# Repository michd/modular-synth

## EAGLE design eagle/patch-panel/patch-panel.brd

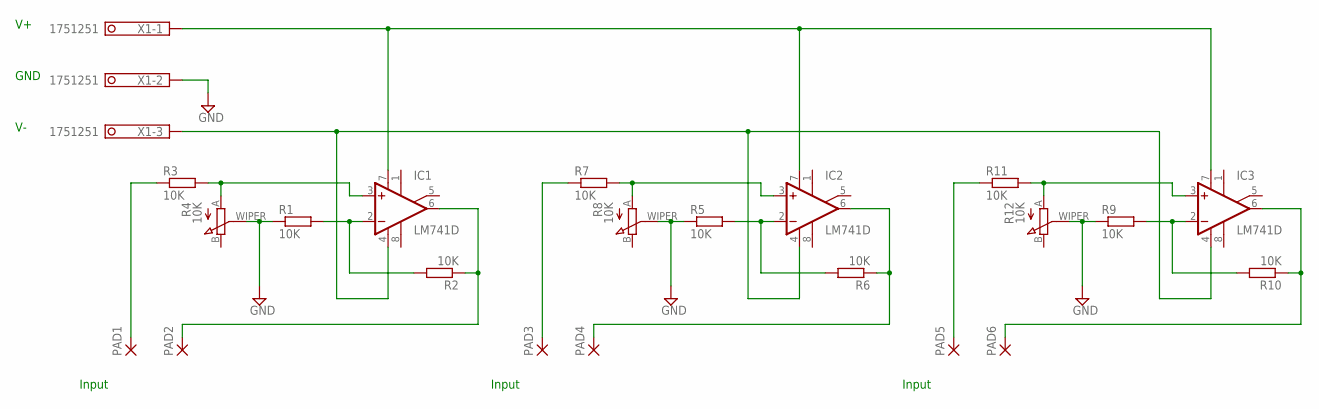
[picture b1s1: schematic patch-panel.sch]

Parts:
IC1, IC2, IC3: LM741D; SO08
PAD1, PAD2, PAD3, PAD4, PAD5, PAD6: 2,54/1,0
R1, R2, R3, R5, R6, R7, R9, R10, R11: 10K; M1206
R4, R8, R12: 10K; PTVA09A-4
X1: 1751251

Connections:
unnamed: IC1.2 (-IN), R1.2, R2.2
unnamed: IC1.6 (OUT), PAD2.1, R2.1
unnamed: IC1.3 (+IN), R3.2, R4.A
unnamed: R1.1, R4.WIPER, R5.1, R8.WIPER, R9.1, R12.WIPER, X1.2
unnamed: PAD1.1, R3.1
unnamed: IC2.2 (-IN), R5.2, R6.2
unnamed: IC2.6 (OUT), PAD4.1, R6.1
unnamed: IC2.3 (+IN), R7.2, R8.A
unnamed: PAD3.1, R7.1
unnamed: IC1.7 (V+), IC2.7 (V+), IC3.7 (V+), X1.1
unnamed: IC3.2 (-IN), R9.2, R10.2
unnamed: IC3.6 (OUT), PAD6.1, R10.1
unnamed: IC3.3 (+IN), R11.2, R12.A
unnamed: PAD5.1, R11.1
unnamed: IC1.4 (V-), IC2.4 (V-), IC3.4 (V-), X1.3

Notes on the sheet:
GND
Input

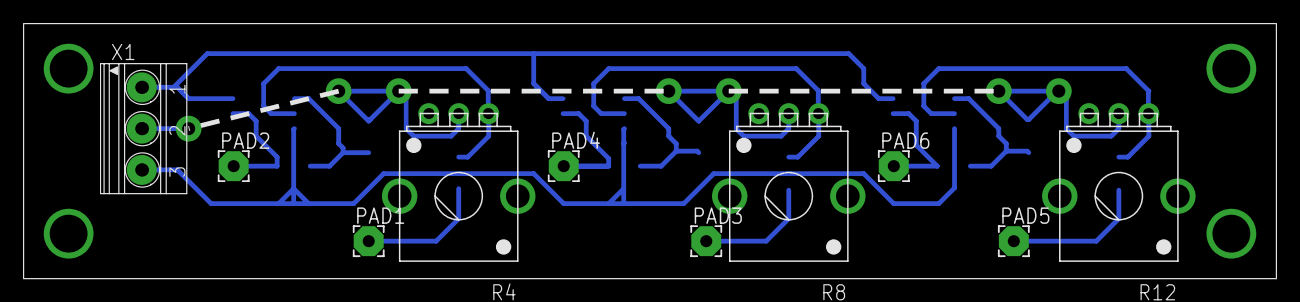
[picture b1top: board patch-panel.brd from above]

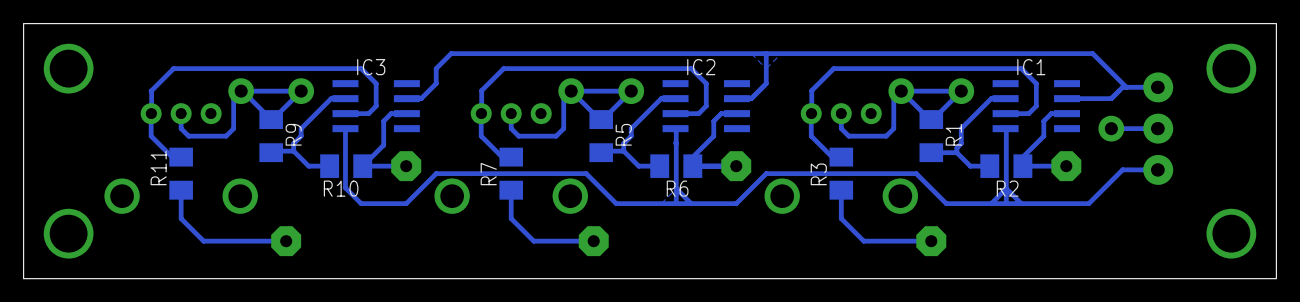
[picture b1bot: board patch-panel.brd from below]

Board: 2 copper layers, 106.0 x 21.6 mm, 22 parts (12 on the bottom side), 15 nets.

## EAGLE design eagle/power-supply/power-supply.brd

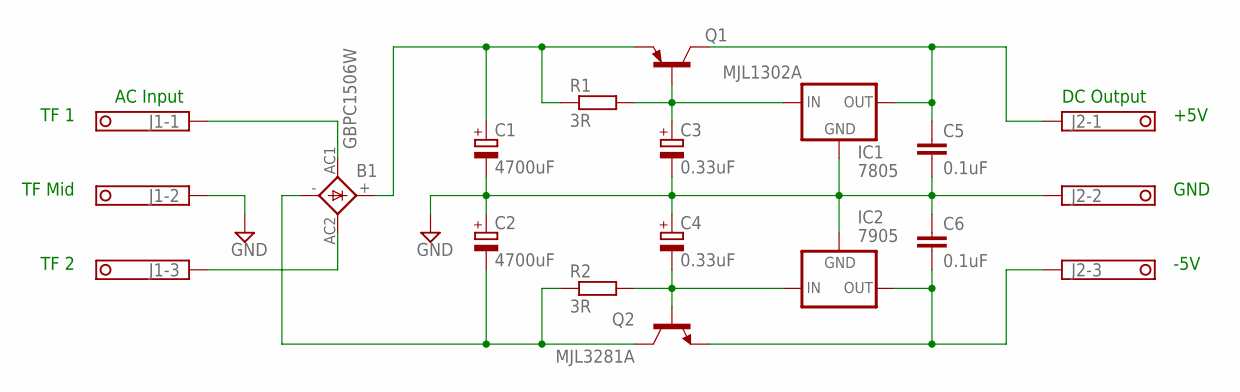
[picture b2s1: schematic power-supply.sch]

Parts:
B1: GBPC1506W; GBPC6
C1, C2: 4700uF; E7,5-16
C3, C4: 0.33uF; E2,5-5
C5, C6: 0.1uF; C102-054X133
IC1: 7805; 78XXS
IC2: 7905; 79XXS
J1, J2: 1751251
Q1: MJL1302A; TO-264
Q2: MJL3281A; TO-264
R1, R2: 3R; 0411/15

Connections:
GND: C1.-, C2.+, C3.-, C4.+, C5.2, C6.1, IC1.GND, IC2.GND, J1.2, J2.2
unnamed: B1.AC1, J1.1
unnamed: B1.AC2, J1.3
unnamed: B1.+, C1.+, Q1.EMITTER, R1.1
unnamed: C3.+, IC1.IN, Q1.BASE, R1.2
unnamed: C5.1, IC1.OUT, J2.1, Q1.COLLECTOR
unnamed: C4.-, IC2.IN, Q2.BASE, R2.2
unnamed: B1.-, C2.-, Q2.COLLECTOR, R2.1
unnamed: C6.2, IC2.OUT, J2.3, Q2.EMITTER

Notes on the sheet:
AC Input
DC Output
GND
+5V
-5V
TF 1
TF Mid
TF 2

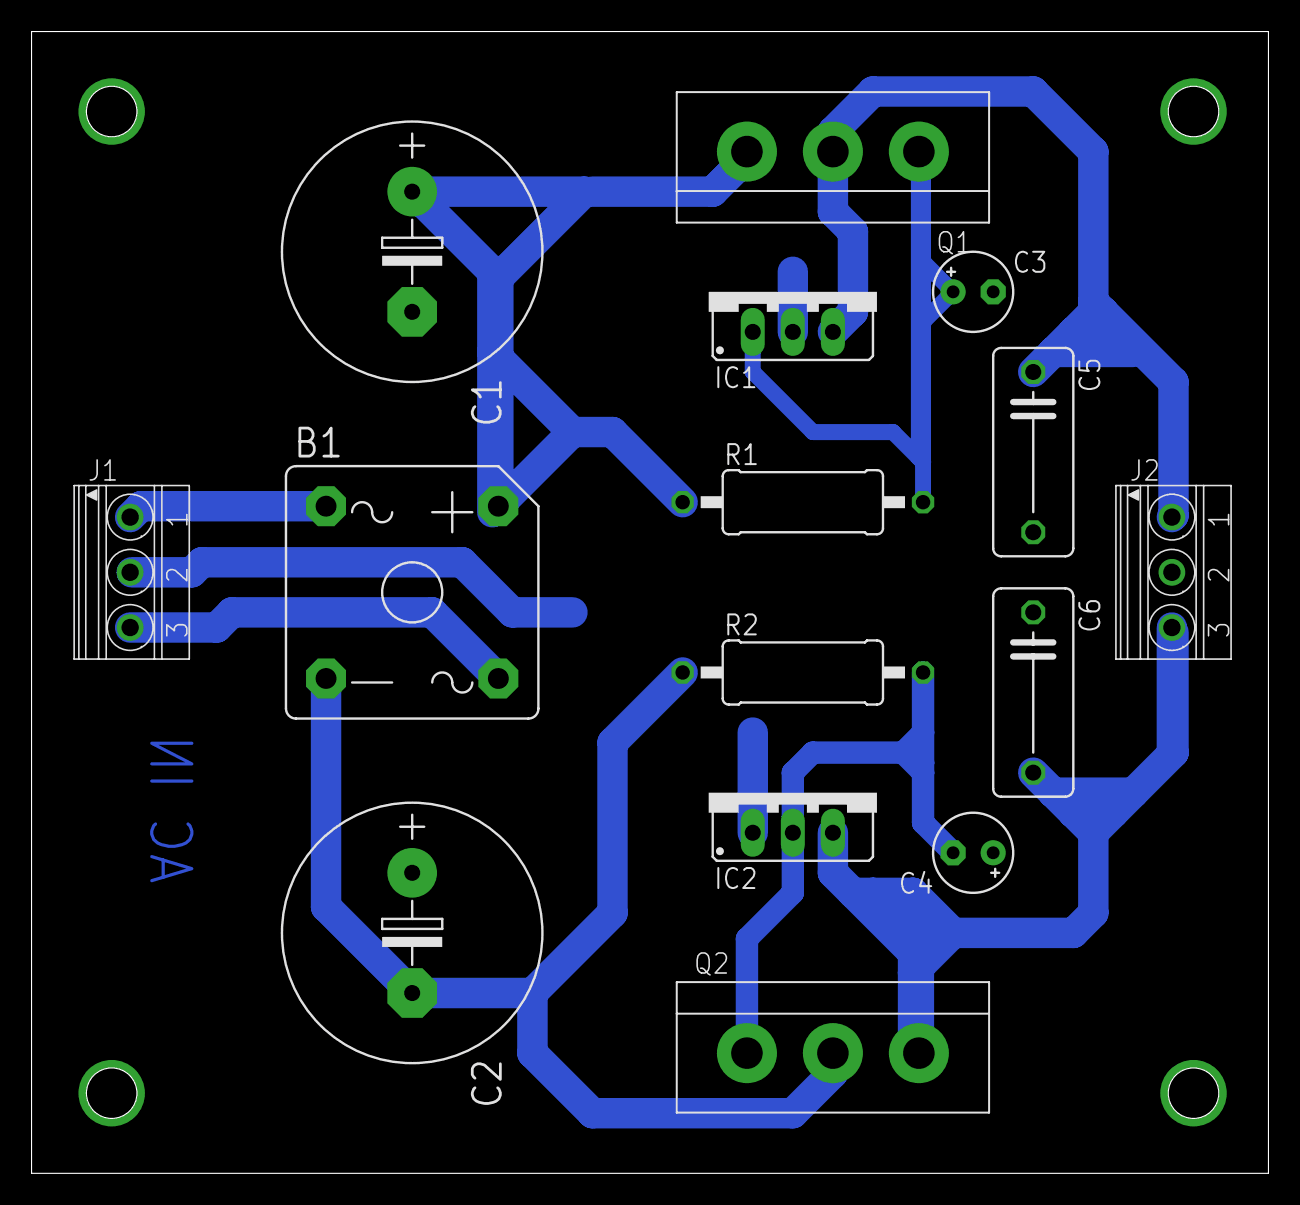
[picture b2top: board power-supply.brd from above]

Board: 2 copper layers, 78.4 x 72.4 mm, 15 parts (0 on the bottom side), 9 nets.

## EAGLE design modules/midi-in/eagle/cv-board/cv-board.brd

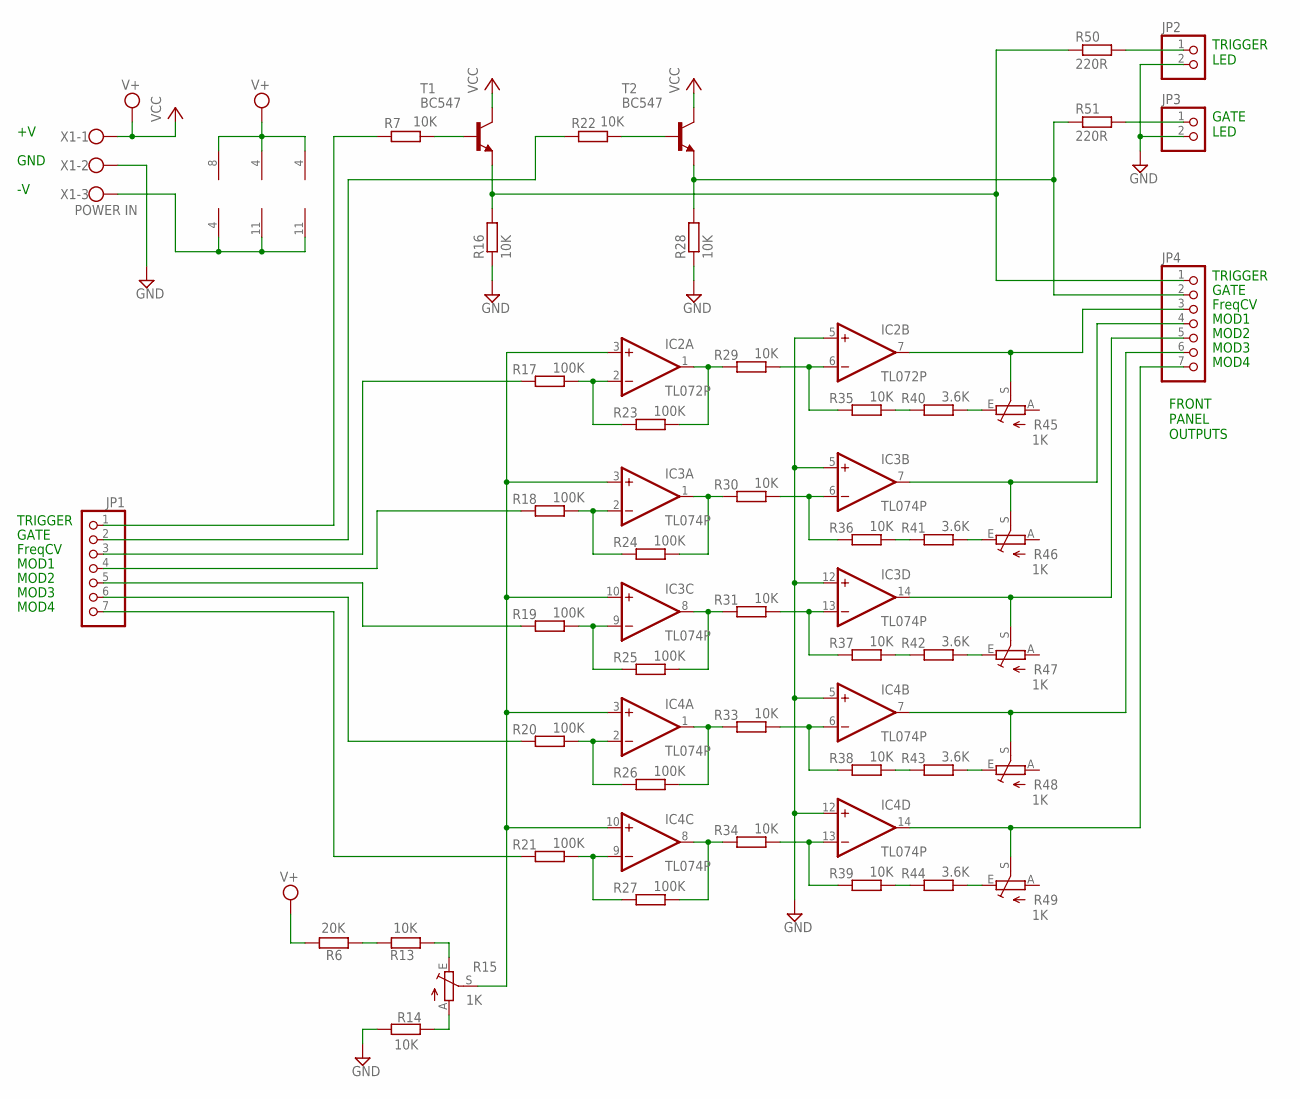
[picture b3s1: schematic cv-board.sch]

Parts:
IC2: TL072P; DIL08
IC3, IC4: TL074P; DIL14
JP1, JP4: PINHD-1X7; 1X07
JP2, JP3: PINHD-1X2; 1X02
R6: 20K; 0207/7
R7, R13, R14, R16, R22, R28, R29, R30, R31, R33, R34, R35, R36, R37, R38, R39: 10K; 0207/7
R15, R45, R46, R47, R48, R49: 1K; CA6V
R17, R18, R19, R20, R21, R23, R24, R25, R26, R27: 100K; 0207/7
R40, R41, R42, R43, R44: 3.6K; 0207/7
R50, R51: 220R; 0207/7
T1, T2: BC547; TO92
X1: POWER IN; W237-103

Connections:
GND: IC2.5 (+IN), IC3.5 (+IN), IC3.12 (+IN), IC4.5 (+IN), IC4.12 (+IN), JP2.2, JP3.2, R14.1, R16.1, R28.1, X1.2
unnamed: IC4.6 (-IN), R33.2, R38.1
unnamed: IC4.2 (-IN), R20.2, R26.1
unnamed: IC2.3 (+IN), IC3.3 (+IN), IC3.10 (+IN), IC4.3 (+IN), IC4.10 (+IN), R15.S
unnamed: JP1.1, R7.1
unnamed: JP1.2, R22.1
unnamed: JP1.3, R17.1
unnamed: JP1.4, R18.1
unnamed: JP1.5, R19.1
unnamed: JP1.6, R20.1
unnamed: JP1.7, R21.1
unnamed: R7.2, T1.2 (B)
unnamed: JP4.1, R16.2, R50.1, T1.1 (E)
unnamed: R22.2, T2.2 (B)
unnamed: JP4.2, R28.2, R51.1, T2.1 (E)
unnamed: IC4.1 (OUT), R26.2, R33.1
unnamed: IC2.2 (-IN), R17.2, R23.1
unnamed: IC3.2 (-IN), R18.2, R24.1
unnamed: IC3.9 (-IN), R19.2, R25.1
unnamed: IC2.8 (V+), IC3.4 (V+), IC4.4 (V+), R6.2, T1.3 (C), T2.3 (C), X1.1
unnamed: IC4.9 (-IN), R21.2, R27.1
unnamed: IC2.1 (OUT), R23.2, R29.1
unnamed: IC2.6 (-IN), R29.2, R35.1
unnamed: IC3.1 (OUT), R24.2, R30.1
unnamed: IC3.6 (-IN), R30.2, R36.1
unnamed: IC3.8 (OUT), R25.2, R31.1
unnamed: IC3.13 (-IN), R31.2, R37.1
unnamed: IC4.8 (OUT), R27.2, R34.1
unnamed: IC4.13 (-IN), R34.2, R39.1
unnamed: IC2.4 (V-), IC3.11 (V-), IC4.11 (V-), X1.3
unnamed: R14.2, R15.A
unnamed: R6.1, R13.2
unnamed: R13.1, R15.E
unnamed: R35.2, R40.1
unnamed: R36.2, R41.1
unnamed: R37.2, R42.1
unnamed: R38.2, R43.1
unnamed: R39.2, R44.1
unnamed: R40.2, R45.E
unnamed: R41.2, R46.E
unnamed: R42.2, R47.E
unnamed: R43.2, R48.E
unnamed: R44.2, R49.E
unnamed: IC2.7 (OUT), JP4.3, R45.S
unnamed: IC3.7 (OUT), JP4.4, R46.S
unnamed: IC3.14 (OUT), JP4.5, R47.S
unnamed: IC4.7 (OUT), JP4.6, R48.S
unnamed: IC4.14 (OUT), JP4.7, R49.S
unnamed: JP2.1, R50.2
unnamed: JP3.1, R51.2

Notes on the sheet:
TRIGGER
GATE
FreqCV
MOD1
MOD2
MOD3
MOD4
FRONT PANEL OUTPUTS
TRIGGER LED
GATE LED
GND

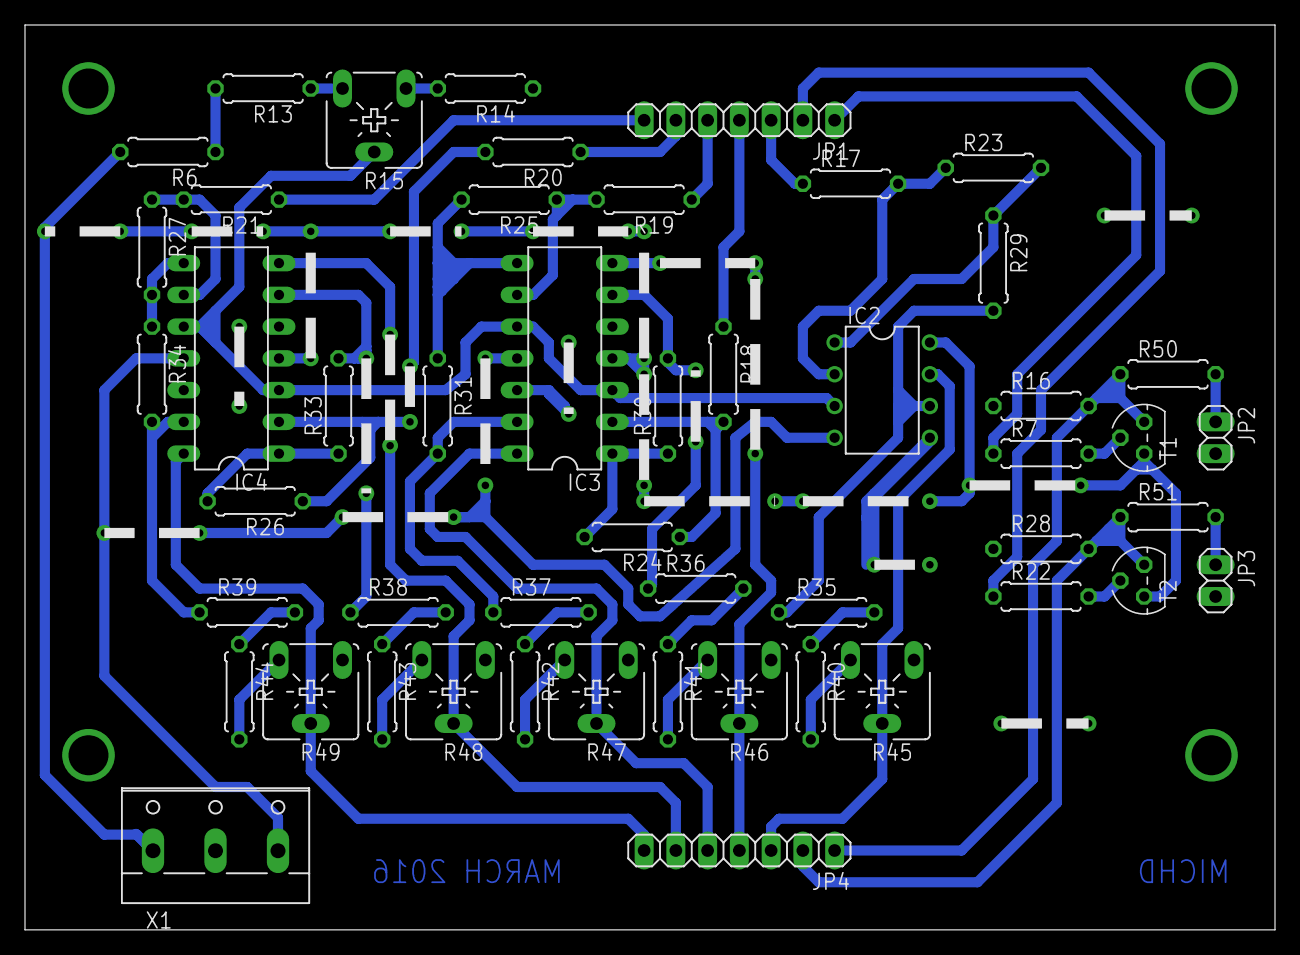
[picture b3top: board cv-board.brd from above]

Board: 2 copper layers, 100.0 x 72.4 mm, 50 parts (0 on the bottom side), 50 nets.

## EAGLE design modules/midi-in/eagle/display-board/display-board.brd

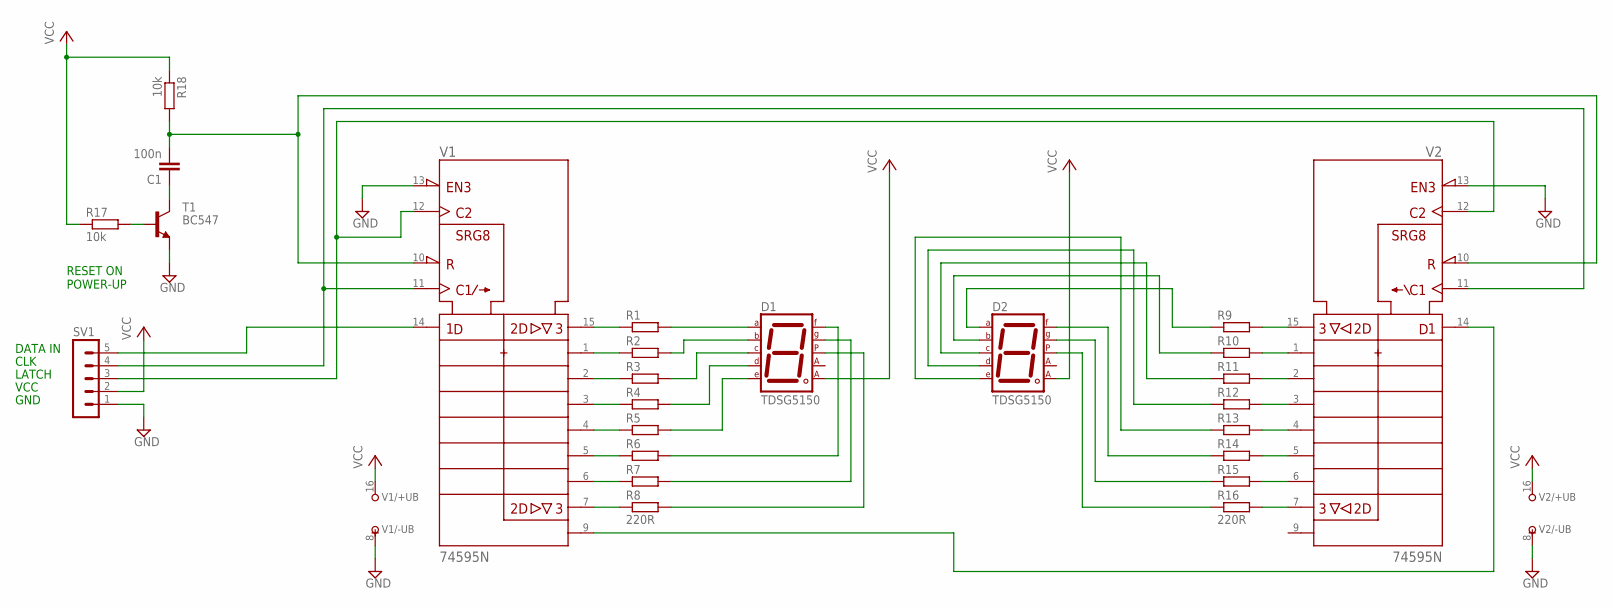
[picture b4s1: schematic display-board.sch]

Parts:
C1: 100n; C050-024X044
D1, D2: TDSG5150; 7SEG-13
R1, R2, R3, R4, R5, R6, R7, R9, R10, R11, R12, R13, R14, R15: R-EU_0207/7; 0207/7
R8, R16: 220R; 0207/7
R17, R18: 10k; 0207/7
SV1: MA05-1
T1: BC547; TO92
V1, V2: 74595N; DIL16

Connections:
unnamed: D1.7 (A), R1.2
unnamed: D1.6 (B), R2.2
unnamed: D1.4 (C), R3.2
unnamed: D1.2 (D), R4.2
unnamed: D1.1 (E), R5.2
unnamed: D1.9 (F), R6.2
unnamed: D1.10 (G), R7.2
unnamed: D1.5 (DP), R8.2
unnamed: D2.7 (A), R9.1
unnamed: D2.6 (B), R10.1
unnamed: D2.4 (C), R11.1
unnamed: D2.2 (D), R12.1
unnamed: D2.1 (E), R13.1
unnamed: D2.9 (F), R14.1
unnamed: D2.10 (G), R15.1
unnamed: D2.5 (DP), R16.1
unnamed: R1.1, V1.15 (QA)
unnamed: R2.1, V1.1 (QB)
unnamed: R3.1, V1.2 (QC)
unnamed: R4.1, V1.3 (QD)
unnamed: R5.1, V1.4 (QE)
unnamed: R6.1, V1.5 (QF)
unnamed: R7.1, V1.6 (QG)
unnamed: R8.1, V1.7 (QH)
unnamed: R9.2, V2.15 (QA)
unnamed: R10.2, V2.1 (QB)
unnamed: R11.2, V2.2 (QC)
unnamed: R12.2, V2.3 (QD)
unnamed: R13.2, V2.4 (QE)
unnamed: R14.2, V2.5 (QF)
unnamed: R15.2, V2.6 (QG)
unnamed: R16.2, V2.7 (QH)
unnamed: V1.9 (QH*), V2.14 (SER)
unnamed: C1.2, R18.2, V1.10 (!SRCLR), V2.10 (!SRCLR)
unnamed: SV1.3, V1.12 (RCK), V2.12 (RCK)
unnamed: SV1.4, V1.11 (SRCK), V2.11 (SRCK)
unnamed: R17.2, T1.2 (B)
unnamed: SV1.5, V1.14 (SER)
unnamed: SV1.1, T1.1 (E), V1.8 (-UB), V1.13 (!G), V2.8 (-UB), V2.13 (!G)
unnamed: C1.1, T1.3 (C)
VCC: D1.8 (CA2), D2.8 (CA2), R17.1, R18.1, SV1.2, V1.16 (+UB), V2.16 (+UB)

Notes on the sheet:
RESET ON POWER-UP
DATA IN
CLK
LATCH
VCC
GND

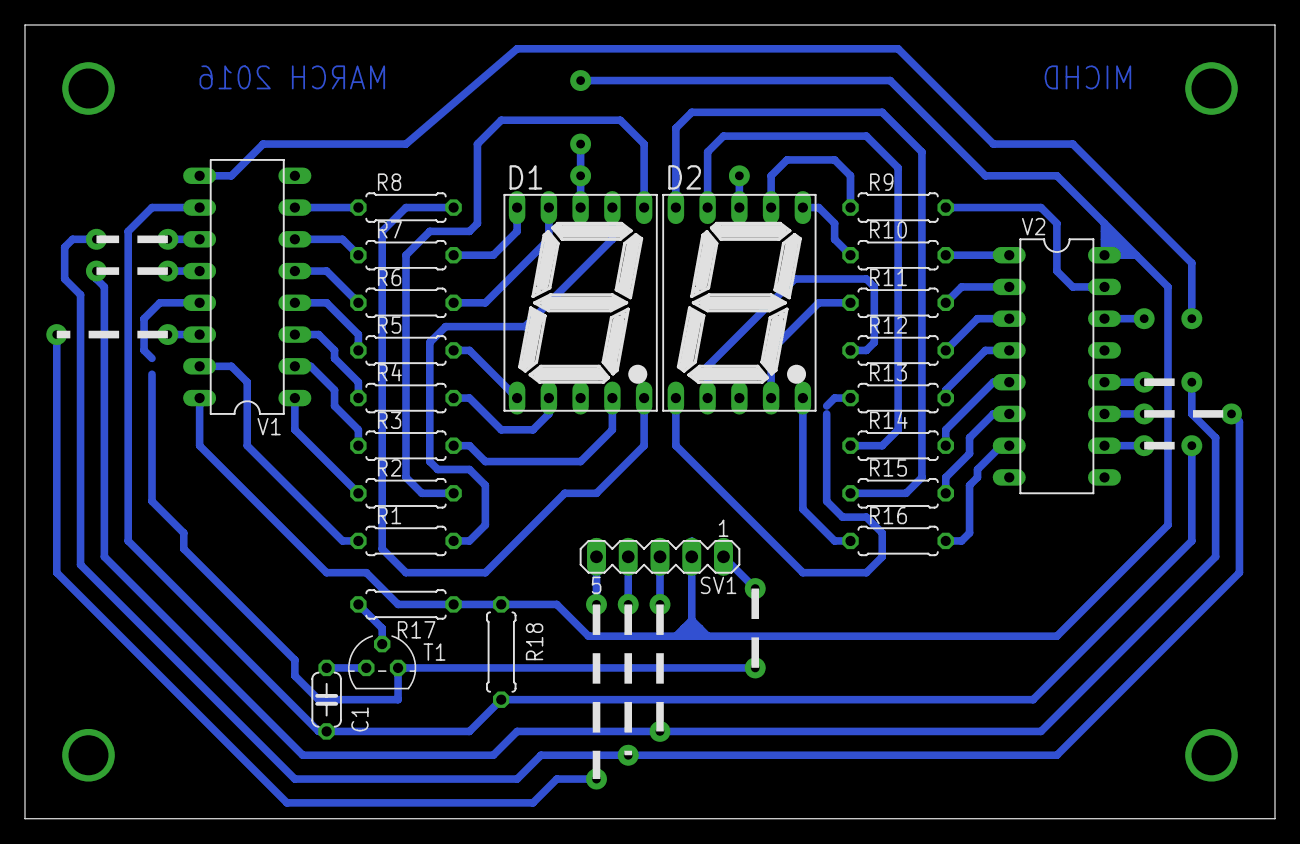
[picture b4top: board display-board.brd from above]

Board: 2 copper layers, 100.0 x 63.5 mm, 25 parts (0 on the bottom side), 41 nets.
